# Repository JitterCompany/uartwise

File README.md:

# uartwise
SerialLogger Hardware

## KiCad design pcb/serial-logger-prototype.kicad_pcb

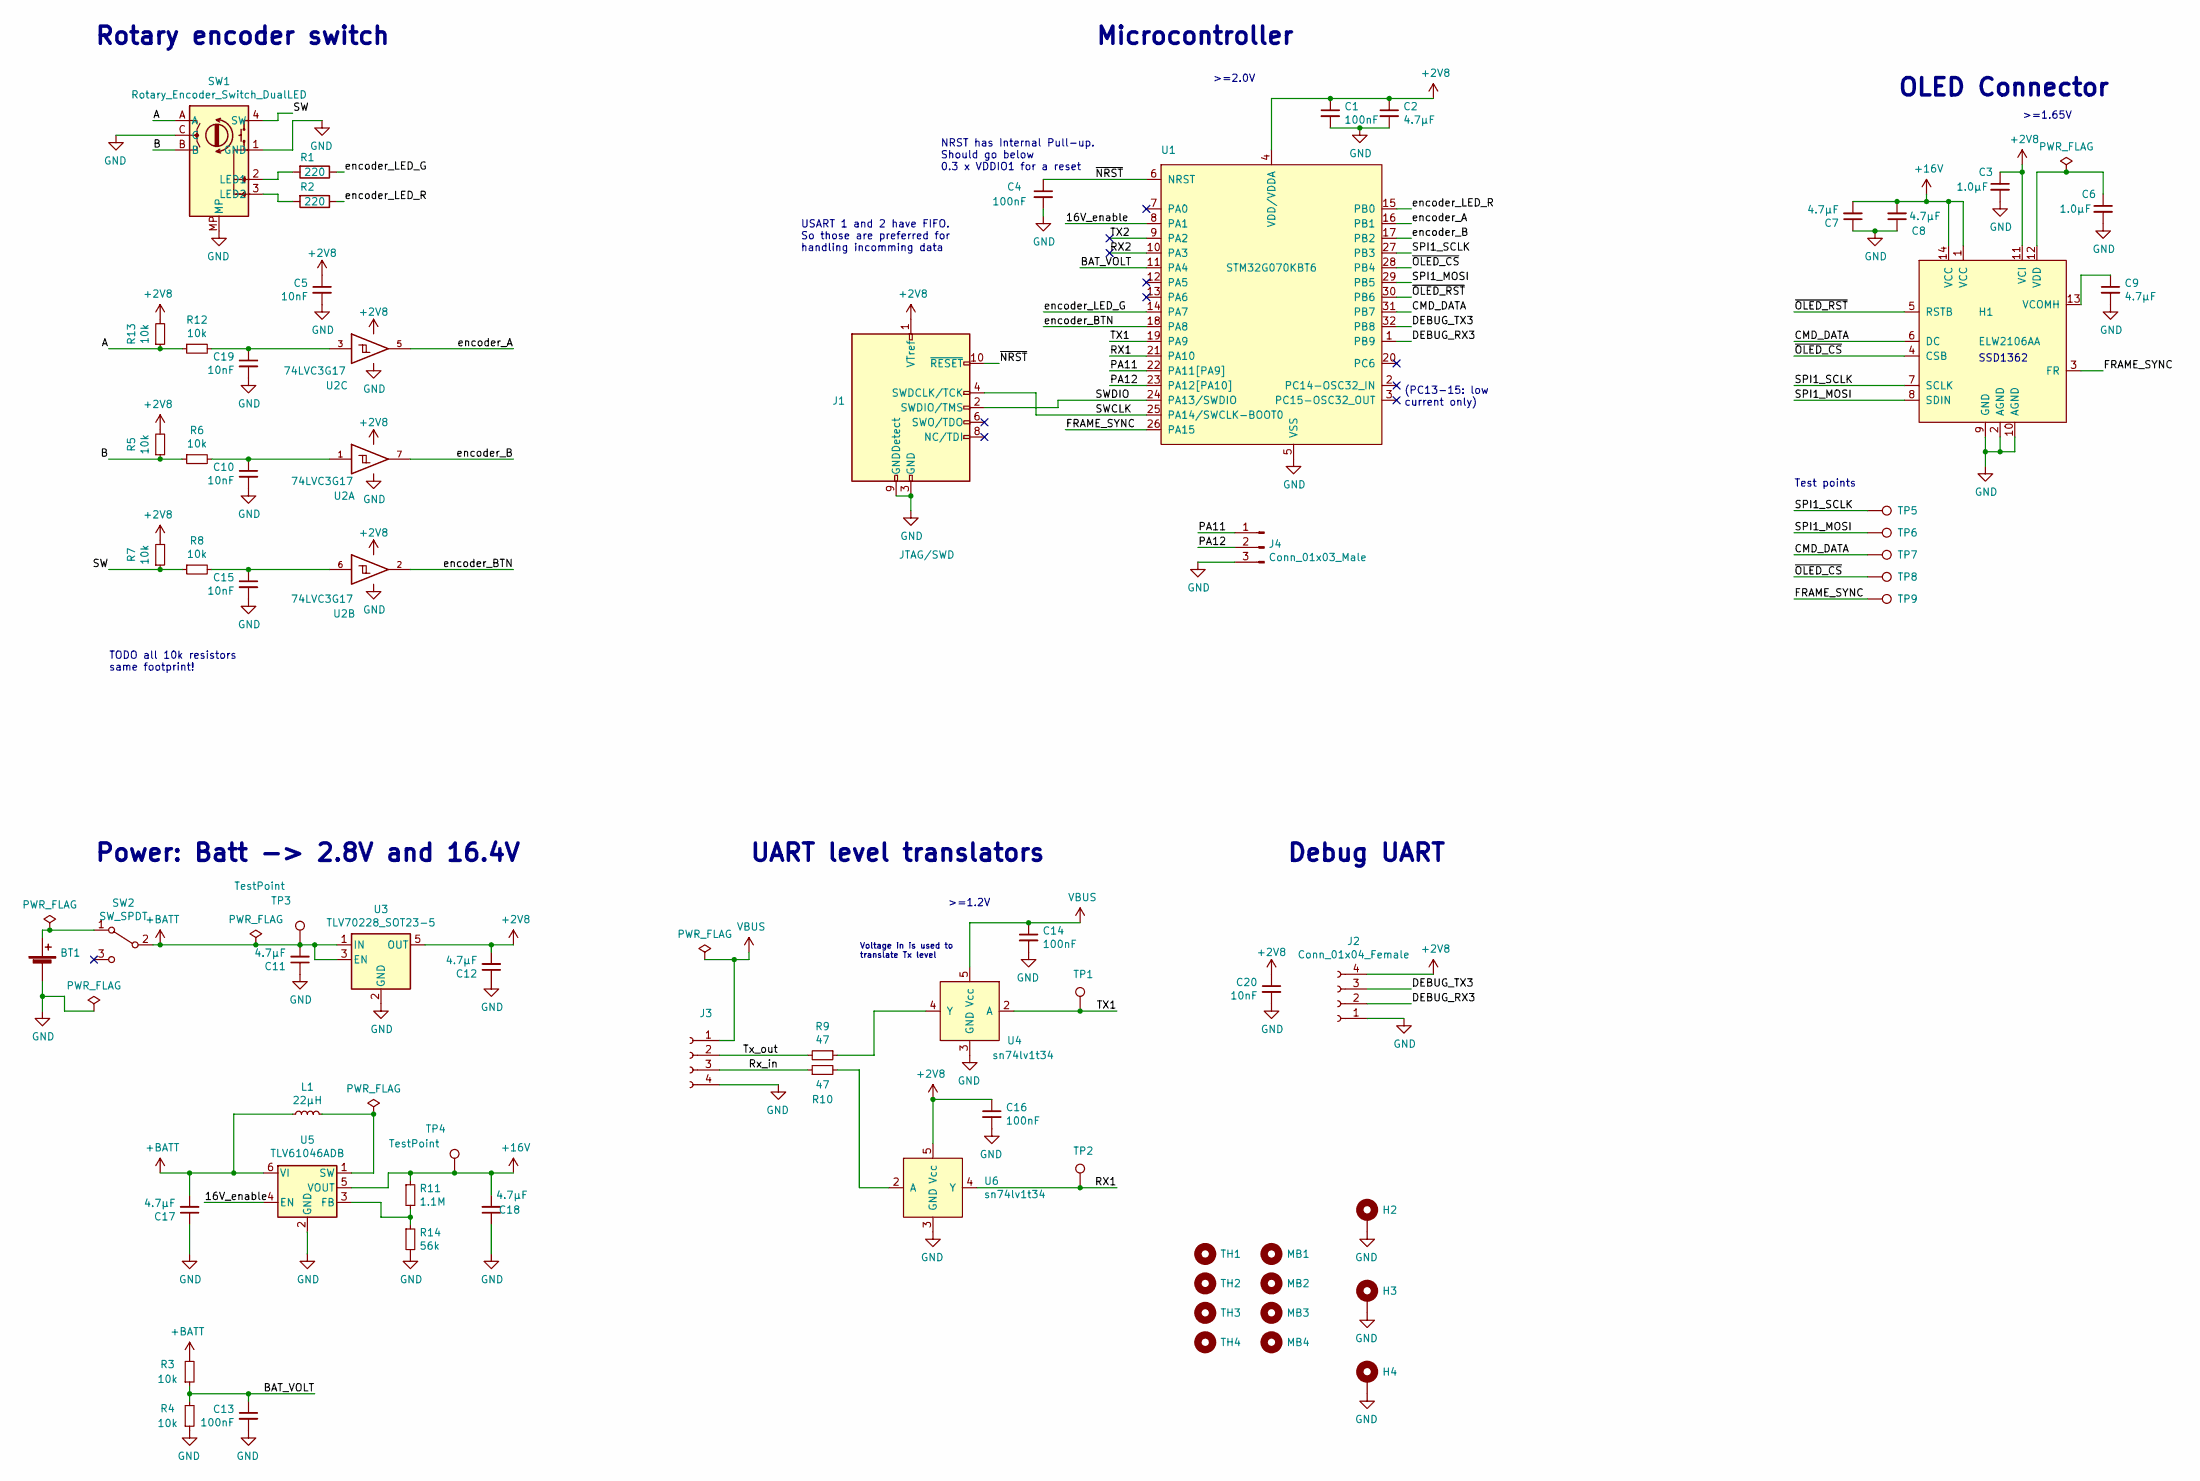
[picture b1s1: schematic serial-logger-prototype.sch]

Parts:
BT1: Battery_Cell; BatteryHolder_Keystone_1043(p)_1x18650; MPN 1043P; Mouser 534-1043P
C1, C4, C13, C14, C16: 100nF; C_0402_1005Metric
C2, C7, C8, C9, C11, C12, C17, C18: 4.7µF; C_0805_2012Metric
C3, C6: 1.0µF; C_0603_1608Metric
C5, C10, C15, C19, C20: 10nF; C_0402_1005Metric
H1: ELW2106AA; Molex_503480-1400-1x14-1MP_P0.5mm_Horizontal; MPN 503480-1400; Farnell 3215747
H2, H3, H4: DNI; MountingHole_2.2mm_M2_Pad_Via
J1: JTAG/SWD; PinHeader_2x05_P1.27mm_Vertical_SMD; MPN FTSH-105-01-L-DV-K-P; Farnell 2856437
J2: Conn_01x04_Female; PinSocket_1x04_P2.54mm_Vertical; Farnell 1593460
J3: Conn_01x04_Male; PinHeader_1x04_P2.54mm_Horizontal; Farnell 2888929
J4: Conn_01x03_Male; PinHeader_1x03_P2.54mm_Vertical
L1: 22µH; L_1812_4532Metric; MPN LQH43PN220M26L; Farnell 2219279
MB1, MB2, MB3, MB4: DNI; MouseBite_3.5mmx2.2mm_breakaway
R1, R2: 220; R_0402_1005Metric
R3, R4, R6, R8, R12: 10k; R_0402_1005Metric
R5, R7, R13: 10k; R_0603_1608Metric
R9, R10: 47; R_0402_1005Metric
R11: 1.1M; R_0402_1005Metric
R14: 56k; R_0402_1005Metric
SW1: Rotary_Encoder_Switch_DualLED; PEL12D-4xxxS-Sxxxx; MPN PEL12D-4225S-S2024; Mouser 652-PEL12D4225SS2024
SW2: SW_SPDT; slide_switch_09.03201.02; MPN 09.03201.02; Farnell 1608080
TH1, TH2, TH3, TH4: DNI; Tooling_hole_4mm_4.04mm_paste
TP1, TP2, TP5, TP6, TP7, TP8, TP9: TestPoint; TestPoint_Pad_D1.0mm
TP3, TP4: TestPoint; TestPoint_Pad_D1.5mm
U1: STM32G070KBT6; LQFP-32_7x7mm_P0.8mm; MPN STM32G070KBT6; Farnell 3365394
U2: 74LVC3G17; TSSOP-8_3x3mm_P0.65mm; MPN SN74LVC3G17DCT; Farnell 1236391
U3: TLV70228_SOT23-5; SOT-23-5; MPN TLV70228DBVT; Farnell 2492371
U4, U6: sn74lv1t34; SOT-23-5; MPN SN74LV1T34DBVR; Mouser 595-SN74LV1T34DBVR
U5: TLV61046ADB; SOT-23-6; MPN TLV61046ADBV; Farnell 3007283

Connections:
+2V8: C1.1, C2.1, C3.1, C5.1, C12.2, C16.1, C20.1, H1.11 (VCI), J1.1 (VTref), J2.4, R5.2, R7.2, R13.2, U1.4 (VDD/VDDA), U2.8 (VCC), U3.5 (OUT), U6.5 (Vcc)
+16V: C7.2, C8.2, C18.2, H1.1 (VCC), H1.14 (VCC), R11.1, TP4.1, U5.5 (VOUT)
+BATT: C11.2, C17.2, L1.1, R3.2, SW2.2 (B), TP3.1, U3.1 (IN), U3.3 (EN), U5.6 (VI)
/16V_enable: U1.8 (PA1), U5.4 (EN)
/A: R12.1, R13.1, SW1.A
/B: R5.1, R6.1, SW1.B
/BAT_VOLT: C13.1, R3.1, R4.2, U1.11 (PA4)
/CMD_DATA: H1.6 (DC), TP7.1, U1.31 (PB7)
/DEBUG_RX3: J2.2, U1.1 (PB9)
/DEBUG_TX3: J2.3, U1.32 (PB8)
/FRAME_SYNC: H1.3 (FR), TP9.1, U1.26 (PA15)
/PA11: J4.1, U1.22 (PA11[PA9])
/PA12: J4.2, U1.23 (PA12[PA10])
/RX1: TP2.1, U1.21 (PA10), U6.4 (Y)
/Rx_in: J3.3, R10.1
/SPI1_MOSI: H1.8 (SDIN), TP6.1, U1.29 (PB5)
/SPI1_SCLK: H1.7 (SCLK), TP5.1, U1.27 (PB3)
/SW: R7.1, R8.1, SW1.4 (SW)
/SWCLK: J1.4 (SWDCLK/TCK), U1.25 (PA14/SWCLK-BOOT0)
/SWDIO: J1.2 (SWDIO/TMS), U1.24 (PA13/SWDIO)
/TX1: TP1.1, U1.19 (PA9), U4.2 (A)
/Tx_out: J3.2, R9.2
/encoder_A: U1.16 (PB1), U2.5
/encoder_B: U1.17 (PB2), U2.7
/encoder_BTN: U1.18 (PA8), U2.2
/encoder_LED_G: R1.1, U1.14 (PA7)
/encoder_LED_R: R2.1, U1.15 (PB0)
/~NRST: C4.1, J1.10 (~RESET~), U1.6 (NRST)
/~OLED_CS: H1.4 (CSB), TP8.1, U1.28 (PB4)
/~OLED_RST: H1.5 (RSTB), U1.30 (PB6)
GND: BT1.2 (-), C1.2, C2.2, C3.2, C4.2, C5.2, C6.2, C7.1, C8.1, C9.2, C10.2, C11.1, C12.1, C13.2, C14.2, C15.2, C16.2, C17.1, C18.1, C19.2, C20.2, H1.2 (AGND), H1.9 (GND), H1.10 (AGND), H2.1, H3.1, H4.1, J1.3 (GND), J1.5 (GND), J1.9 (GNDDetect), J2.1, J3.4, J4.3, R4.1, R14.2, SW1.1 (GND), SW1.C, SW1.MP, U1.5 (VSS), U2.4 (GND), U3.2 (GND), U4.3 (GND), U5.2 (GND), U6.3 (GND)
unnamed: BT1.1 (+), SW2.1 (A)
unnamed: C6.1, H1.12 (VDD)
unnamed: C9.1, H1.13 (VCOMH)
unnamed: C10.1, R6.2, U2.1
unnamed: C15.1, R8.2, U2.6
unnamed: C19.1, R12.2, U2.3
unnamed: L1.2, U5.1 (SW)
unnamed: R1.2, SW1.2 (LED1)
unnamed: R2.2, SW1.3 (LED2)
unnamed: R9.1, U4.4 (Y)
unnamed: R10.2, U6.2 (A)
unnamed: R11.2, R14.1, U5.3 (FB)
VBUS: C14.1, J3.1, U4.5 (Vcc)

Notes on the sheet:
USART 1 and 2 have FIFO. So those are preferred for handling incomming data
NRST has Internal Pull-up. Should go below 0.3 x VDDIO1 for a reset
SSD1362
OLED Connector
Microcontroller
Power: Batt -> 2.8V and 16.4V
UART level translators
Voltage in is used to translate Tx level
Debug UART
>=1.65V
>=1.2V
>=2.0V
(PC13-15: low current only)
Rotary encoder switch
Test points
TODO all 10k resistors same footprint!

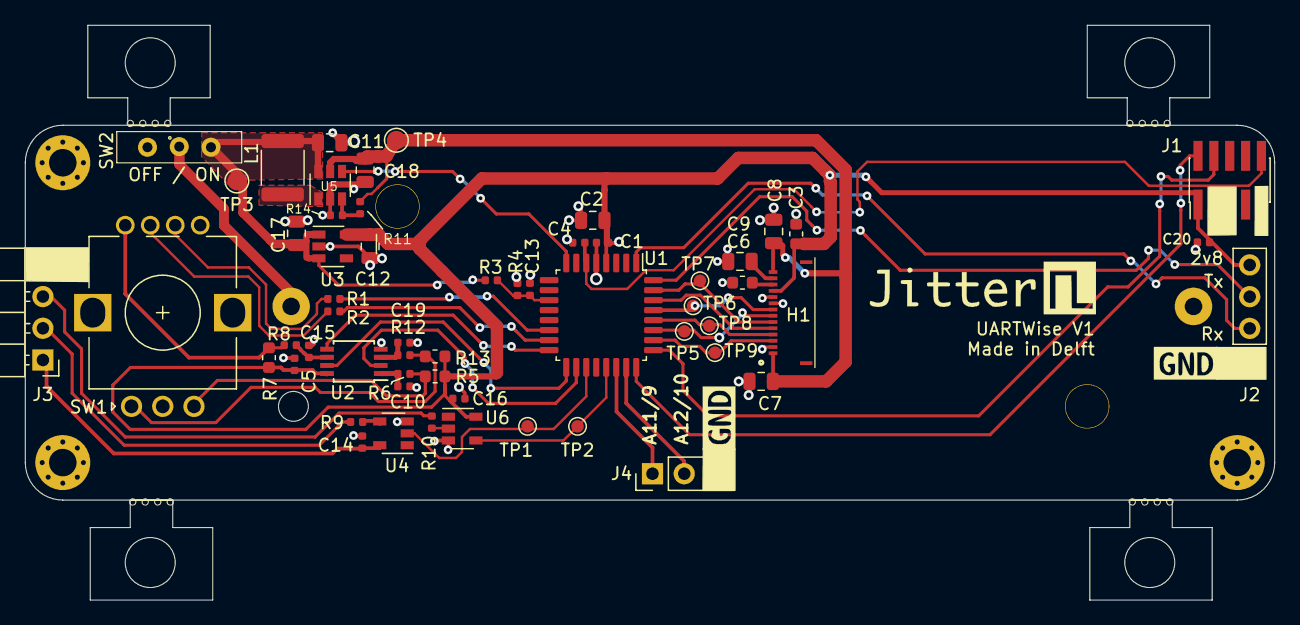
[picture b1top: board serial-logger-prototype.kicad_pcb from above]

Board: 2 copper layers, 100.0 x 46.0 mm, 69 parts (1 on the bottom side), 44 nets.

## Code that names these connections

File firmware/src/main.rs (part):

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    spi::Spi<
        SPI1,
        (
            gpio::gpiob::PB3<gpio::Input<gpio::Floating>>,
            gpio::gpioa::PA6<gpio::Input<gpio::Floating>>,
            gpio::gpiob::PB5<gpio::Input<gpio::Floating>>
        )
    >,
    gpio::gpiob::PB7<gpio::Output<gpio::PushPull>>,
    gpio::gpiob::PB4<gpio::Output<gpio::PushPull>>
    >,
    Font6x8
    >;
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
    struct Resources {
        terminal: Terminal,
        led_r: gpio::gpiob::PB0<gpio::Output<gpio::PushPull>>,
        led_g: gpio::gpioa::PA7<gpio::Output<gpio::PushPull>>,
        timer: Timer<stm32::TIM1>,
        exti: EXTI,
        encoder: Enc,
        tx: serial::Tx<stm32::USART1, FullConfig>,
        rx: serial::Rx<stm32::USART1, FullConfig>,
        uart_in_buffer: ArrayString::<[u8; 1024]>,
        debug_pin1: gpio::gpiob::PB8<gpio::Output<gpio::PushPull>>,
        debug_pin2: gpio::gpiob::PB9<gpio::Output<gpio::PushPull>>,
        debug_pin3: gpio::gpioa::PA11<gpio::Output<gpio::PushPull>>,
        debug_pin4: gpio::gpioa::PA12<gpio::Output<gpio::PushPull>>,
        delay: Delay<TIM15>
    }

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

        // let mut led = gpioa.pa5.into_push_pull_output();
        let mut led_g = gpioa.pa7.into_push_pull_output();
        let led_r = gpiob.pb0.into_push_pull_output();
        let mut en_16v = gpioa.pa1.into_push_pull_output();

        let mut exti = dp.EXTI;

        let encoder = {
            let encoder_a = gpiob.pb1.listen( gpio::SignalEdge::Rising, &mut exti).downgrade();
            let encoder_b = gpiob.pb2.listen(gpio::SignalEdge::Rising, &mut exti).downgrade();
            Encoder::new(encoder_a, encoder_b)
        };

        let btn = gpioa.pa8.into_pull_up_input();
        btn.listen(gpio::SignalEdge::Falling, &mut exti);

        let mut cs = gpiob.pb4.into_push_pull_output(); // blue 13
        cs.set_high().unwrap();

        // d/c pin for toggling between data/cmd
        // dc low = command, dc high = data
        let mut dc = gpiob.pb7.into_push_pull_output(); // orange
        dc.set_low().unwrap();

        let mut rst = gpiob.pb6.into_push_pull_output();
        rst.set_high().unwrap();

        let mut usart = dp.USART1.usart( gpioa.pa9, gpioa.pa10,
            FullConfig::default()
                .baudrate(115200.bps())
                .fifo_enable()
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        delay.delay(2500.ms());
        led_g.set_low().unwrap();

        let sck = gpiob.pb3; // yellow 10
        let miso = gpioa.pa6; //not used
        let mosi = gpiob.pb5; // green 9
        let spi = dp.SPI1.spi(
            (sck, miso, mosi),
            spi::MODE_0,
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
        // rx.listen();

        let mut debug_pin1 = gpiob.pb8.into_push_pull_output();
        debug_pin1.set_low().unwrap();

        let mut debug_pin2 = gpiob.pb9.into_push_pull_output();
        debug_pin2.set_low().unwrap();

        let mut debug_pin3 = gpioa.pa11.into_push_pull_output();
        debug_pin3.set_low().unwrap();

        let mut debug_pin4 = gpioa.pa12.into_push_pull_output();
        debug_pin4.set_low().unwrap();

        cx.spawn.startup().ok();
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
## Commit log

2020-01-08 Add pcb directory
2020-01-08 Finish schematics (for now)
    All footprints complete except on/off switch (depends on enclosure)
    TODO: pin swapping for easier routing
2020-01-08 First Trial placement of components on pcb
2020-01-09 Layout seems plausible: start routing
2020-01-10 Finish routing and pin swapping
2020-01-10 Improve some routing
2020-01-10 Update slide switch placement and add mounting hole
2020-01-10 Uptimize component placement to make room for enclosure
2020-01-10 Add silklayer at bottom side
2020-01-10 Add rounded corners to board outline
2020-01-10 Fix silk screen overlap
2020-01-29 Fix typo in filenames
2020-01-29 Add note about PC13-15
2020-01-30 Schematics: implement BATT_VOLT, shuffle schematics blocks around
2020-01-30 Add pinMapping xlsx sheet
2020-01-30 Add working proof of concept for ELW2106AA OLED display
    Based on SSD1362 driver IC
2020-02-04 PCB: tweak placements + silk screen
2020-02-04 PCB: finalize design (DRC pass)
2020-02-04 PCB: cleanup layout, optimize for 3d enclosure
2020-02-04 Add lasercut drawings + all production files
2020-02-04 Schematics: annotate
2020-02-05 Production gerber: rename to include dimensions
2020-02-05 Production gerber: rename to correct dimensions...
2020-02-05 Implement OLED Command Enum.
    Based on SSD1306 crate, but with correct values.
2020-02-10 Add Final production BOM
2020-02-10 Fix BOM: add display as separate item
2020-03-20 unknown layout update
2020-06-05 listen to pn interrupts from encoder and button
2020-06-05 Start real seriallogger firmware
2020-06-05 Create encoder object and clean up a bit
2020-07-01 Basic example of uart -> oled
    However the uart interrupt is not handled fast enough causing overrun
    errors. Even on optimize=2 with baudrate 9600. Next step is to implement
    DMA to overcome this issue.
2020-07-08 Schematics: add note for next revision
2020-08-07 Fix uart overrun issue.
    The problem was that ALL interrupts are disabled when any .lock() is
    issued inside any task. By rearranging priorites, we now don't need a
    lock on terminal.render(). So the critical sections are minimized so
    that the uart interrupt is not unecessary blocked.
    This is an issue with RTIC on Cortex M0.
2020-08-07 Update to use rtic
